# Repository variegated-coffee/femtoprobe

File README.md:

# Femtoprobe

*Femtoprobe R2A, rendered in KiCad.*

The Femtoprobe is an ultra-compact SWD and UART debug probe for [APEC SoM](https://github.com/variegated-coffee/apec-som) carrier boards, built around the RP2040. It's smaller than a Picoprobe, and it connects to the host through one of the APEC SoM's built-in USB hub ports, so a single USB-C cable to the carrier board carries both the controller's USB and the debug probe.

The Femtoprobe is either meant to be fitted on a pin header during development and removed when it's no longer needed, or to be soldered on using the castellated pins. It isn't as feature-rich as the Raspberry Pi Debug Probe or as sophisticated as a J-Link; its strengths are simplicity and size.

## High-level features

* RP2040 microcontroller with 2 MB of QSPI flash and a 12 MHz crystal, the same flash and crystal as the Raspberry Pi Pico
* USB full-speed device interface on the castellations
* SWD (SWCLK, SWDIO) and UART (TX, RX) target interface, with 100 Ω series resistors
* Runs from a 3.3 V supply provided by the carrier
* BOOT and RESET pads for entering the USB bootloader
* 27.93 × 12.13 mm, 4 layers, 8 castellated pins on a 2.54 mm pitch; the pins also take ordinary 2.54 mm pin headers

## Firmware

The Femtoprobe is intended to be used with the [Raspberry Pi Debug Probe firmware](https://github.com/raspberrypi/debugprobe). The board *does* however use different IO assignments, and as such, a small firmware patch is provided in [firmware-patch.diff](firmware-patch.diff).

## Project status

The current hardware revision is R2A. It hasn't been manufactured yet, and you probably shouldn't be the first one to do it. The earlier engineering validation revisions, EV1, have been manufactured;

## Documentation

* [ENGINEERING-NOTES.md](ENGINEERING-NOTES.md): pinout, power, interfaces and carrier-board design
* [MANUFACTURING-NOTES.md](MANUFACTURING-NOTES.md): fabrication, assembly and bring-up

## Notice

This repository contains design files only. It is not a finished product, and it has not been tested or certified for compliance with any regulation, including but not limited to CE, UKCA or FCC requirements.

Anyone who manufactures, assembles, or places a product based on these files on the market does so as the manufacturer of that product, and is solely responsible for its safety, conformity assessment, marking, documentation, and any legal obligations that follow. If you build or use it yourself, you do so at your own risk.

The designs are provided “as is” under the CERN-OHL-P v2. See sections 5.1 and 5.2 for the disclaimer of warranty and limitation of liability.

## License

The design files and documentation in this repository are licensed under the CERN Open Hardware Licence Version 2 – Permissive (CERN-OHL-P-2.0); see [LICENSE.txt](LICENSE.txt).

The schematic and PCB contain copies of symbols, footprints and 3D model references from the KiCad libraries, which keep their own licence; see [THIRD_PARTY.md](THIRD_PARTY.md).

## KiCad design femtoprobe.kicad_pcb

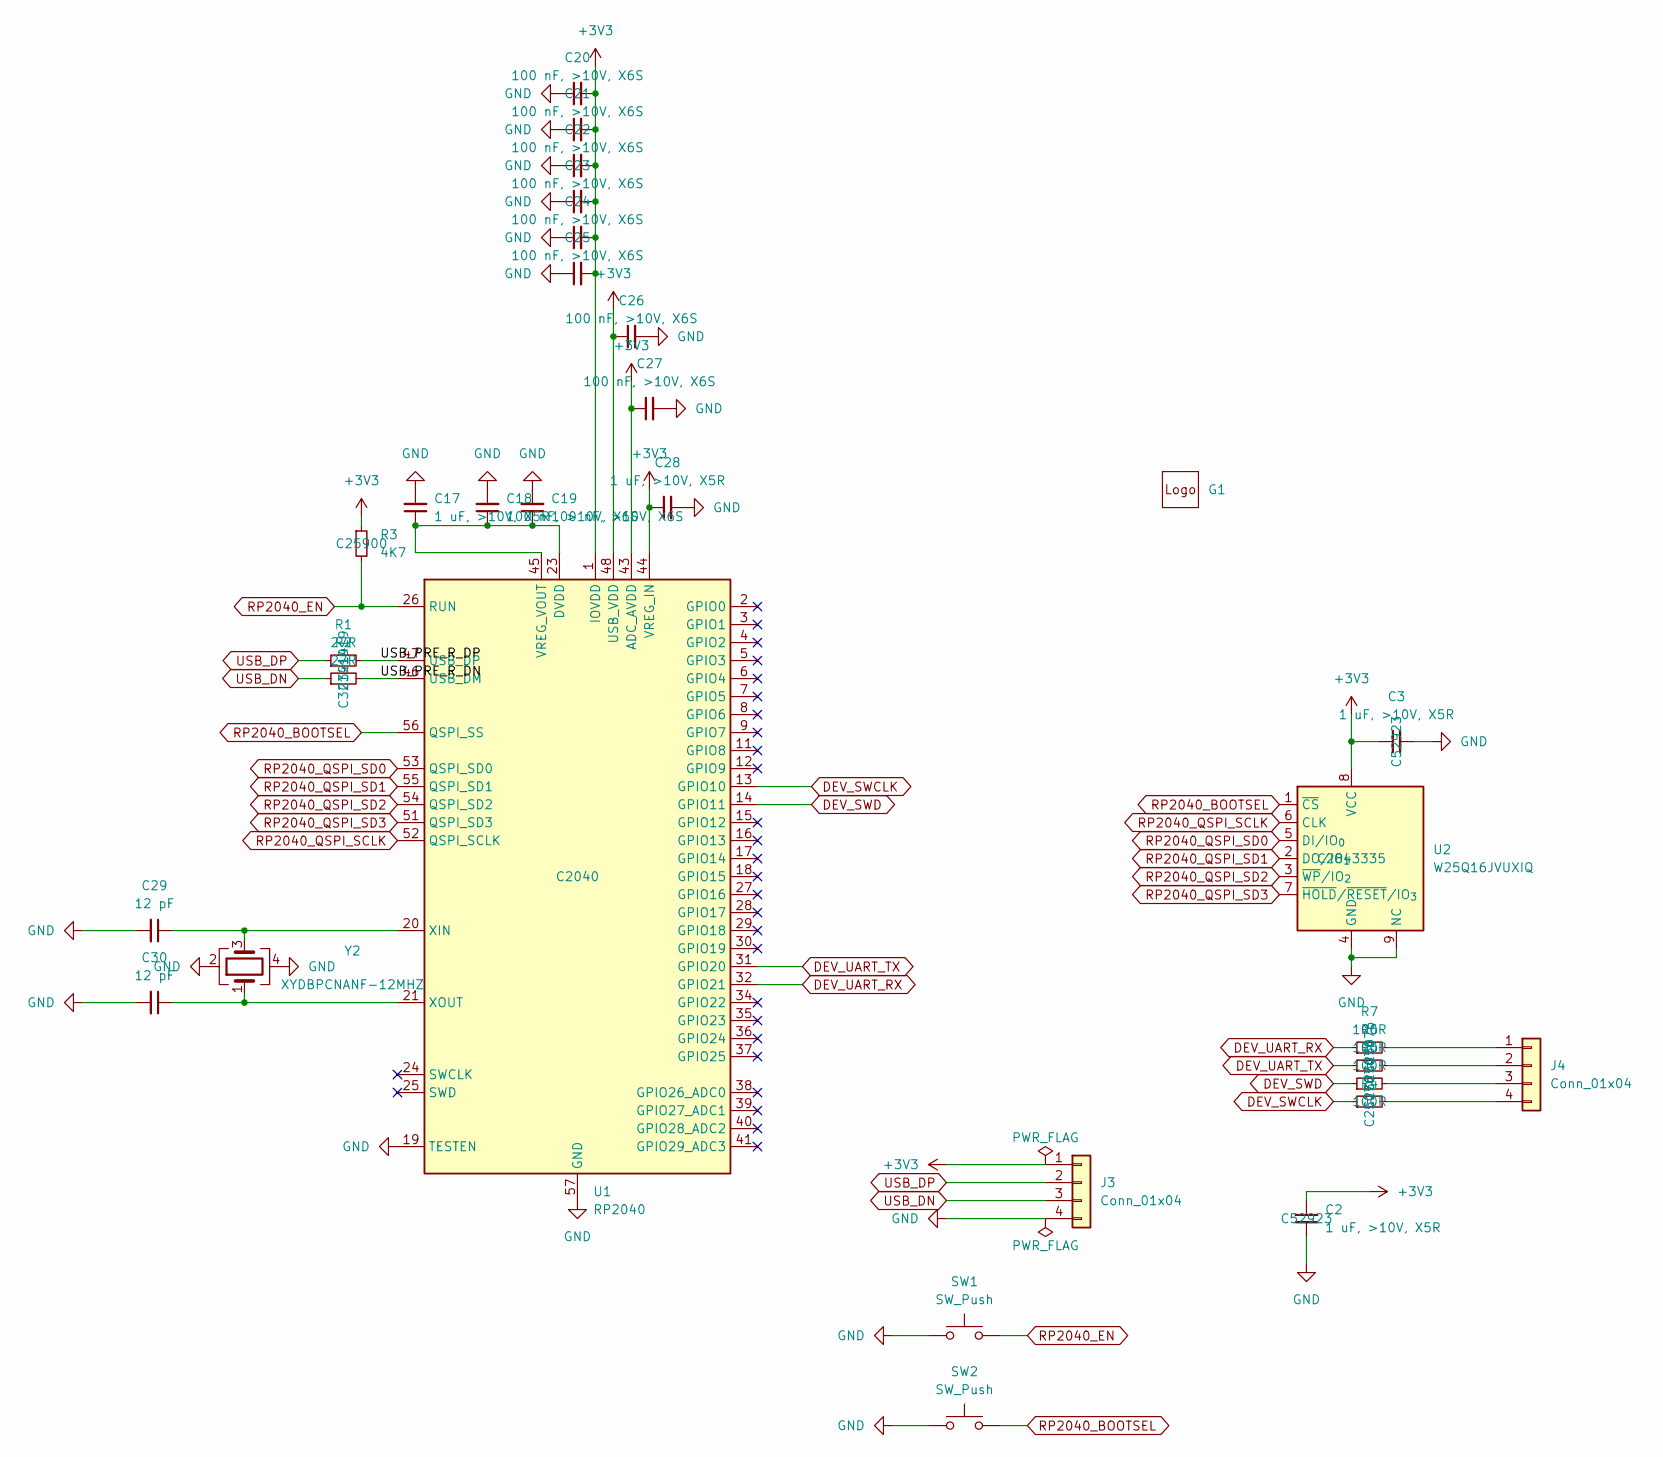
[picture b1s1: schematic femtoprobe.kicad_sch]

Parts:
C2, C3: 1 uF, >10V, X5R; C_0402_1005Metric; LCSC C52923
C17, C28: 1 uF, >10V, X5R; C_0402_1005Metric; JLCPCB Basic N
C18, C19, C20, C21, C22, C23, C24, C25, C26, C27: 100 nF, >10V, X6S; C_0402_1005Metric; JLCPCB Basic N
C29, C30: 12 pF; C_0402_1005Metric; LCSC C1547
G1: VariegatedCoffeeLogo_Micro
J3, J4: Conn_01x04; PinHeader_2x04_P2.54mm_Vertical
R1, R2: 27R; R_0402_1005Metric; LCSC C321419
R3: 4K7; R_0402_1005Metric; LCSC C25900
R4, R5, R6, R7: 100R; R_0402_1005Metric; LCSC C25076
SW1, SW2: SW_Push; PinHeader_1x02_P1.00mm_Vertical
U1: RP2040; QFN-56-1EP_7x7mm_P0.4mm_EP3.2x3.2mm; LCSC C2040
U2: W25Q16JVUXIQ; Winbond_USON-8-1EP_3x2mm_P0.5mm_EP0.2x1.6mm; LCSC C2843335
Y2: XYDBPCNANF-12MHZ; Crystal_SMD_2520-4Pin_2.5x2.0mm; LCSC C521567

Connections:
/USB_PRE_R_DN: R2.2, U1.46 (USB_DM)
/USB_PRE_R_DP: R1.2, U1.47 (USB_DP)
DEV_SWCLK: R4.1, U1.13 (GPIO10)
DEV_SWD: R5.1, U1.14 (GPIO11)
DEV_UART_RX: R7.1, U1.32 (GPIO21)
DEV_UART_TX: R6.1, U1.31 (GPIO20)
unnamed: J4.1, R7.2
unnamed: J4.2, R6.2
unnamed: J4.3, R5.2
unnamed: J4.4, R4.2
unnamed: C17.1, C18.1, C19.1, U1.23 (DVDD), U1.45 (VREG_VOUT), U1.50 (DVDD)
unnamed: C29.1, U1.20 (XIN), Y2.3
unnamed: C30.1, U1.21 (XOUT), Y2.1
RP2040_BOOTSEL: SW2.2, U1.56 (QSPI_SS), U2.1 (~CS)
RP2040_EN: R3.2, SW1.2, U1.26 (RUN)
RP2040_QSPI_SCLK: U1.52 (QSPI_SCLK), U2.6 (CLK)
RP2040_QSPI_SD0: U1.53 (QSPI_SD0), U2.5 (DI/IO_{0})
RP2040_QSPI_SD1: U1.55 (QSPI_SD1), U2.2 (DO/IO_{1})
RP2040_QSPI_SD2: U1.54 (QSPI_SD2), U2.3 (~WP/IO_{2})
RP2040_QSPI_SD3: U1.51 (QSPI_SD3), U2.7 (~HOLD/~RESET/IO_{3})
USB_DN: J3.3, R2.1
USB_DP: J3.2, R1.1

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
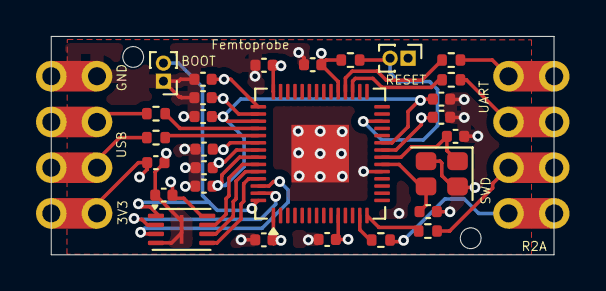
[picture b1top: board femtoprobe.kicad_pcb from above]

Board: 4 copper layers, 27.9 x 12.1 mm, 33 parts (1 on the bottom side), 24 nets.

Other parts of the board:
H1, H2: (no value)
